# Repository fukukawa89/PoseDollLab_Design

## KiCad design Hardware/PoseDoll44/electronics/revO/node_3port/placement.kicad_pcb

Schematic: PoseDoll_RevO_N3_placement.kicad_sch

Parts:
C1: 10u X5R 25V / CL21A106KAYNNNE; C_0805_2012Metric
C2, C4: 22u X5R 16V / CL21A226MOYNNNE; C_0805_2012Metric
C3, C5, C7, C21, C22, C23: 100n X7R; C_0603_1608Metric
C6: 1u X7R; C_0603_1608Metric
D1: PESD5V0S2BT,215; SOT-23
J1: Fused 5V branch; NOT 12V qualified; JST_PH_B2B-PH-SM4-TB_1x02-1MP_P2.00mm_Vertical
J2: CAN IN / GND-L-H; JST_GH_BM03B-GHS-TBT_1x03-1MP_P1.25mm_Vertical
J3: CAN OUT / GND-L-H; JST_GH_BM03B-GHS-TBT_1x03-1MP_P1.25mm_Vertical
J11: P1 sensor / CS GPIO2; JST_SH_BM06B-SRSS-TB_1x06-1MP_P1.00mm_Vertical
J12: P2 sensor / CS GPIO4; JST_SH_BM06B-SRSS-TB_1x06-1MP_P1.00mm_Vertical
J13: P3 sensor / CS GPIO5; JST_SH_BM06B-SRSS-TB_1x06-1MP_P1.00mm_Vertical
JP1: CAN TERM: close endpoints only; SolderJumper-2_P1.3mm_Open_Pad1.0x1.5mm
L1: LSXND4040TKL2R2MDG / 2.2uH; L_Taiyo-Yuden_NR-40xx
R1, R2, R4, R113, R117, R123, R127, R133, R137: 10k; R_0603_1608Metric
R3, R116, R126, R136: 100k; R_0603_1608Metric
R5: 120R 1% 0.33W / CRCW0603120RFKEAHP; R_0603_1608Metric
R110, R111, R112, R120, R121, R122, R130, R131, R132: 100R; R_0603_1608Metric
R114, R115, R124, R125, R134, R135: 47k; R_0603_1608Metric
TP1: UART_TX; TestPoint_Pad_D1.0mm
TP2: UART_RX; TestPoint_Pad_D1.0mm
TP3: GND; TestPoint_Pad_D1.0mm
TP4: PG; TestPoint_Pad_D1.0mm
TP5: EN; TestPoint_Pad_D1.0mm
TP6: BOOT_N; TestPoint_Pad_D1.0mm
U1: ESP32-S3-WROOM-1-N8; ESP32-S3-WROOM-1
U2: TPS62162DSGR; Texas_DSG0008A_WSON-8-1EP_2x2mm_P0.5mm_EP0.9x1.6mm
U3: TCAN332DR; SOIC-8_3.9x4.9mm_P1.27mm
U11, U12, U13: SN74LVC125APWR; TSSOP-14_4.4x5mm_P0.65mm

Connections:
/+3V3: C2.1, C4.1, C5.1, C7.1, C21.1, C22.1, C23.1, J11.2, J12.2, J13.2, L1.2, R1.1, R2.1, R3.1, R4.1, R113.1, R117.1, R123.1, R127.1, R133.1, R137.1, U1.2 (3V3), U2.6 (VOS), U3.3 (VCC), U11.14 (VCC), U12.14 (VCC), U13.14 (VCC)
/+5V_IN: C1.1, C3.1, J1.1, U2.2 (VIN), U2.3 (EN)
/BOOT_N: R2.2, TP6.1, U1.27 (IO0)
/CAN_H: D1.2 (CAN2), J2.3, J3.3, R5.1, U3.7 (CANH)
/CAN_L: D1.1 (CAN1), J2.2, J3.2, JP1.2 (B), U3.6 (CANL)
/CAN_RX: U1.11 (IO18), U3.4 (RXD)
/CAN_TX: R4.2, U1.10 (IO17), U3.1 (TXD)
/CS1_MCU: R113.2, U1.38 (IO2), U11.1 (1OE_N), U11.4 (2OE_N), U11.10 (3OE_N), U11.12 (4A)
/CS2_MCU: R123.2, U1.4 (IO4), U12.1 (1OE_N), U12.4 (2OE_N), U12.10 (3OE_N), U12.12 (4A)
/CS3_MCU: R133.2, U1.5 (IO5), U13.1 (1OE_N), U13.4 (2OE_N), U13.10 (3OE_N), U13.12 (4A)
/EN: C6.1, R1.2, TP5.1, U1.3 (EN)
/GND: C1.2, C2.2, C3.2, C4.2, C5.2, C6.2, C7.2, C21.2, C22.2, C23.2, D1.3 (GND), J1.2, J2.1, J3.1, J11.1, J12.1, J13.1, R114.2, R115.2, R116.2, R124.2, R125.2, R126.2, R134.2, R135.2, R136.2, TP3.1, U1.1 (GND), U1.40 (GND), U1.41 (GND), U2.1 (PGND), U2.4 (AGND), U2.5 (FB), U2.9 (PAD), U3.2 (GND), U11.7 (GND), U11.13 (4OE_N), U12.7 (GND), U12.13 (4OE_N), U13.7 (GND), U13.13 (4OE_N)
/P1_CS: J11.6, R112.2, R117.2
/P1_CS_DRV: R112.1, U11.11 (4Y)
/P1_MISO: J11.5, R116.1, U11.9 (3A)
/P1_MOSI: J11.4, R111.2, R115.1
/P1_MOSI_DRV: R111.1, U11.6 (2Y)
/P1_SCK: J11.3, R110.2, R114.1
/P1_SCK_DRV: R110.1, U11.3 (1Y)
/P2_CS: J12.6, R122.2, R127.2
/P2_CS_DRV: R122.1, U12.11 (4Y)
/P2_MISO: J12.5, R126.1, U12.9 (3A)
/P2_MOSI: J12.4, R121.2, R125.1
/P2_MOSI_DRV: R121.1, U12.6 (2Y)
/P2_SCK: J12.3, R120.2, R124.1
/P2_SCK_DRV: R120.1, U12.3 (1Y)
/P3_CS: J13.6, R132.2, R137.2
/P3_CS_DRV: R132.1, U13.11 (4Y)
/P3_MISO: J13.5, R136.1, U13.9 (3A)
/P3_MOSI: J13.4, R131.2, R135.1
/P3_MOSI_DRV: R131.1, U13.6 (2Y)
/P3_SCK: J13.3, R130.2, R134.1
/P3_SCK_DRV: R130.1, U13.3 (1Y)
/PG: R3.2, TP4.1, U2.8 (PG)
/SPI_MISO: U1.21 (IO13), U11.8 (3Y), U12.8 (3Y), U13.8 (3Y)
/SPI_MOSI: U1.19 (IO11), U11.5 (2A), U12.5 (2A), U13.5 (2A)
/SPI_SCK: U1.20 (IO12), U11.2 (1A), U12.2 (1A), U13.2 (1A)
/SW_BUCK: L1.1, U2.7 (SW)
/TERM_R: JP1.1 (A), R5.2
/UART_RX: TP2.1, U1.36 (RXD0)
/UART_TX: TP1.1, U1.37 (TXD0)

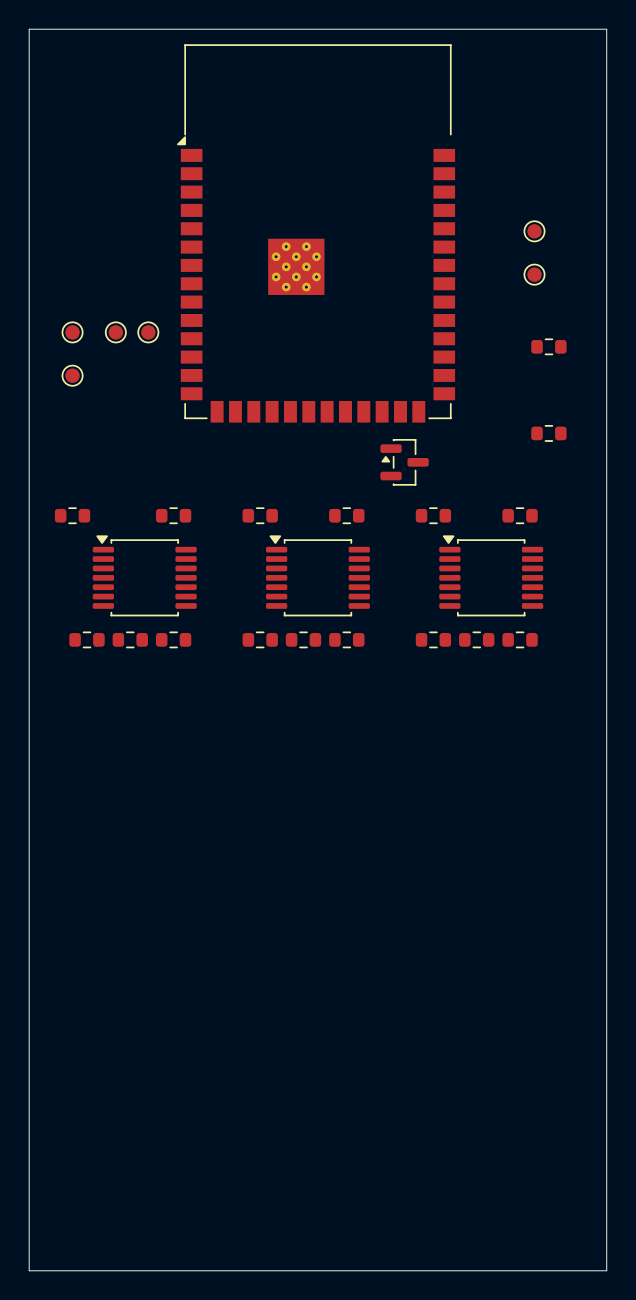
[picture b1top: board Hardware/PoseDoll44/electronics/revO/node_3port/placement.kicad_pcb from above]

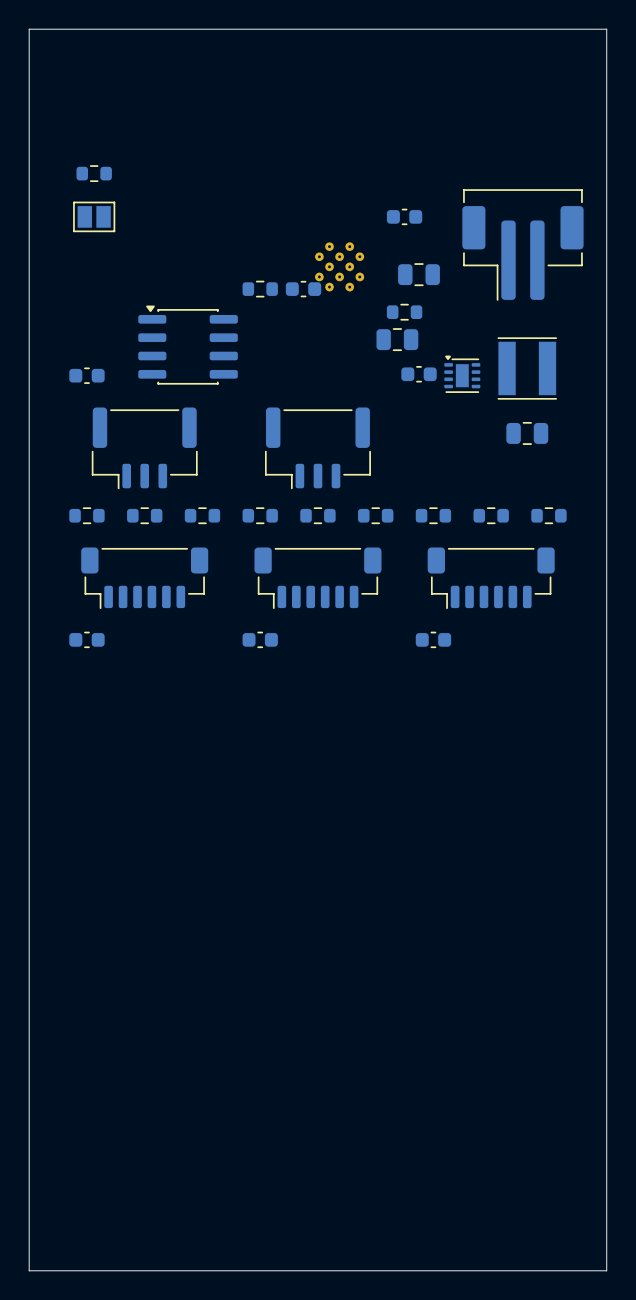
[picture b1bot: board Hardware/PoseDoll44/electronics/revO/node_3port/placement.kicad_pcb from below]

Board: 4 copper layers, 40.0 x 86.0 mm, 60 parts (32 on the bottom side), 41 nets, no tracks yet.

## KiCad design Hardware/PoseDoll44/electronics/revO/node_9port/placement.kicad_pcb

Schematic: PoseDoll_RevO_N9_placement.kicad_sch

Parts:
C1: 10u X5R 25V / CL21A106KAYNNNE; C_0805_2012Metric
C2, C4: 22u X5R 16V / CL21A226MOYNNNE; C_0805_2012Metric
C3, C5, C7, C21, C22, C23, C24, C25, C26, C27, C28, C29: 100n X7R; C_0603_1608Metric
C6: 1u X7R; C_0603_1608Metric
D1: PESD5V0S2BT,215; SOT-23
J1: Fused 5V branch; NOT 12V qualified; JST_PH_B2B-PH-SM4-TB_1x02-1MP_P2.00mm_Vertical
J2: CAN IN / GND-L-H; JST_GH_BM03B-GHS-TBT_1x03-1MP_P1.25mm_Vertical
J3: CAN OUT / GND-L-H; JST_GH_BM03B-GHS-TBT_1x03-1MP_P1.25mm_Vertical
J11: P1 sensor / CS GPIO2; JST_SH_BM06B-SRSS-TB_1x06-1MP_P1.00mm_Vertical
J12: P2 sensor / CS GPIO4; JST_SH_BM06B-SRSS-TB_1x06-1MP_P1.00mm_Vertical
J13: P3 sensor / CS GPIO5; JST_SH_BM06B-SRSS-TB_1x06-1MP_P1.00mm_Vertical
J14: P4 sensor / CS GPIO6; JST_SH_BM06B-SRSS-TB_1x06-1MP_P1.00mm_Vertical
J15: P5 sensor / CS GPIO7; JST_SH_BM06B-SRSS-TB_1x06-1MP_P1.00mm_Vertical
J16: P6 sensor / CS GPIO8; JST_SH_BM06B-SRSS-TB_1x06-1MP_P1.00mm_Vertical
J17: P7 sensor / CS GPIO9; JST_SH_BM06B-SRSS-TB_1x06-1MP_P1.00mm_Vertical
J18: P8 sensor / CS GPIO10; JST_SH_BM06B-SRSS-TB_1x06-1MP_P1.00mm_Vertical
J19: P9 sensor / CS GPIO14; JST_SH_BM06B-SRSS-TB_1x06-1MP_P1.00mm_Vertical
JP1: CAN TERM: close endpoints only; SolderJumper-2_P1.3mm_Open_Pad1.0x1.5mm
L1: LSXND4040TKL2R2MDG / 2.2uH; L_Taiyo-Yuden_NR-40xx
R1, R2, R4, R113, R117, R123, R127, R133, R137, R143, R147, R153, R157, R163, R167, R173, R177, R183, R187, R193, R197: 10k; R_0603_1608Metric
R3, R116, R126, R136, R146, R156, R166, R176, R186, R196: 100k; R_0603_1608Metric
R5: 120R 1% 0.33W / CRCW0603120RFKEAHP; R_0603_1608Metric
R110, R111, R112, R120, R121, R122, R130, R131, R132, R140, R141, R142, R150, R151, R152, R160, R161, R162, R170, R171, R172, R180, R181, R182, R190, R191, R192: 100R; R_0603_1608Metric
R114, R115, R124, R125, R134, R135, R144, R145, R154, R155, R164, R165, R174, R175, R184, R185, R194, R195: 47k; R_0603_1608Metric
TP1: UART_TX; TestPoint_Pad_D1.0mm
TP2: UART_RX; TestPoint_Pad_D1.0mm
TP3: GND; TestPoint_Pad_D1.0mm
TP4: PG; TestPoint_Pad_D1.0mm
TP5: EN; TestPoint_Pad_D1.0mm
TP6: BOOT_N; TestPoint_Pad_D1.0mm
U1: ESP32-S3-WROOM-1-N8; ESP32-S3-WROOM-1
U2: TPS62162DSGR; Texas_DSG0008A_WSON-8-1EP_2x2mm_P0.5mm_EP0.9x1.6mm
U3: TCAN332DR; SOIC-8_3.9x4.9mm_P1.27mm
U11, U12, U13, U14, U15, U16, U17, U18, U19: SN74LVC125APWR; TSSOP-14_4.4x5mm_P0.65mm

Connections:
/+3V3: C2.1, C4.1, C5.1, C7.1, C21.1, C22.1, C23.1, C24.1, C25.1, C26.1, C27.1, C28.1, C29.1, J11.2, J12.2, J13.2, J14.2, J15.2, J16.2, J17.2, J18.2, J19.2, L1.2, R1.1, R2.1, R3.1, R4.1, R113.1, R117.1, R123.1, R127.1, R133.1, R137.1, R143.1, R147.1, R153.1, R157.1, R163.1, R167.1, R173.1, R177.1, R183.1, R187.1, R193.1, R197.1, U1.2 (3V3), U2.6 (VOS), U3.3 (VCC), U11.14 (VCC), U12.14 (VCC), U13.14 (VCC), U14.14 (VCC), U15.14 (VCC), U16.14 (VCC), U17.14 (VCC), U18.14 (VCC), U19.14 (VCC)
/+5V_IN: C1.1, C3.1, J1.1, U2.2 (VIN), U2.3 (EN)
/BOOT_N: R2.2, TP6.1, U1.27 (IO0)
/CAN_H: D1.2 (CAN2), J2.3, J3.3, R5.1, U3.7 (CANH)
/CAN_L: D1.1 (CAN1), J2.2, J3.2, JP1.2 (B), U3.6 (CANL)
/CAN_RX: U1.11 (IO18), U3.4 (RXD)
/CAN_TX: R4.2, U1.10 (IO17), U3.1 (TXD)
/CS1_MCU: R113.2, U1.38 (IO2), U11.1 (1OE_N), U11.4 (2OE_N), U11.10 (3OE_N), U11.12 (4A)
/CS2_MCU: R123.2, U1.4 (IO4), U12.1 (1OE_N), U12.4 (2OE_N), U12.10 (3OE_N), U12.12 (4A)
/CS3_MCU: R133.2, U1.5 (IO5), U13.1 (1OE_N), U13.4 (2OE_N), U13.10 (3OE_N), U13.12 (4A)
/CS4_MCU: R143.2, U1.6 (IO6), U14.1 (1OE_N), U14.4 (2OE_N), U14.10 (3OE_N), U14.12 (4A)
/CS5_MCU: R153.2, U1.7 (IO7), U15.1 (1OE_N), U15.4 (2OE_N), U15.10 (3OE_N), U15.12 (4A)
/CS6_MCU: R163.2, U1.12 (IO8), U16.1 (1OE_N), U16.4 (2OE_N), U16.10 (3OE_N), U16.12 (4A)
/CS7_MCU: R173.2, U1.17 (IO9), U17.1 (1OE_N), U17.4 (2OE_N), U17.10 (3OE_N), U17.12 (4A)
/CS8_MCU: R183.2, U1.18 (IO10), U18.1 (1OE_N), U18.4 (2OE_N), U18.10 (3OE_N), U18.12 (4A)
/CS9_MCU: R193.2, U1.22 (IO14), U19.1 (1OE_N), U19.4 (2OE_N), U19.10 (3OE_N), U19.12 (4A)
/EN: C6.1, R1.2, TP5.1, U1.3 (EN)
/GND: C1.2, C2.2, C3.2, C4.2, C5.2, C6.2, C7.2, C21.2, C22.2, C23.2, C24.2, C25.2, C26.2, C27.2, C28.2, C29.2, D1.3 (GND), J1.2, J2.1, J3.1, J11.1, J12.1, J13.1, J14.1, J15.1, J16.1, J17.1, J18.1, J19.1, R114.2, R115.2, R116.2, R124.2, R125.2, R126.2, R134.2, R135.2, R136.2, R144.2, R145.2, R146.2, R154.2, R155.2, R156.2, R164.2, R165.2, R166.2, R174.2, R175.2, R176.2, R184.2, R185.2, R186.2, R194.2, R195.2, R196.2, TP3.1, U1.1 (GND), U1.40 (GND), U1.41 (GND), U2.1 (PGND), U2.4 (AGND), U2.5 (FB), U2.9 (PAD), U3.2 (GND), U11.7 (GND), U11.13 (4OE_N), U12.7 (GND), U12.13 (4OE_N), U13.7 (GND), U13.13 (4OE_N), U14.7 (GND), U14.13 (4OE_N), U15.7 (GND), U15.13 (4OE_N), U16.7 (GND), U16.13 (4OE_N), U17.7 (GND), U17.13 (4OE_N), U18.7 (GND), U18.13 (4OE_N), U19.7 (GND), U19.13 (4OE_N)
/P1_CS: J11.6, R112.2, R117.2
/P1_CS_DRV: R112.1, U11.11 (4Y)
/P1_MISO: J11.5, R116.1, U11.9 (3A)
/P1_MOSI: J11.4, R111.2, R115.1
/P1_MOSI_DRV: R111.1, U11.6 (2Y)
/P1_SCK: J11.3, R110.2, R114.1
/P1_SCK_DRV: R110.1, U11.3 (1Y)
/P2_CS: J12.6, R122.2, R127.2
/P2_CS_DRV: R122.1, U12.11 (4Y)
/P2_MISO: J12.5, R126.1, U12.9 (3A)
/P2_MOSI: J12.4, R121.2, R125.1
/P2_MOSI_DRV: R121.1, U12.6 (2Y)
/P2_SCK: J12.3, R120.2, R124.1
/P2_SCK_DRV: R120.1, U12.3 (1Y)
/P3_CS: J13.6, R132.2, R137.2
/P3_CS_DRV: R132.1, U13.11 (4Y)
/P3_MISO: J13.5, R136.1, U13.9 (3A)
/P3_MOSI: J13.4, R131.2, R135.1
/P3_MOSI_DRV: R131.1, U13.6 (2Y)
/P3_SCK: J13.3, R130.2, R134.1
/P3_SCK_DRV: R130.1, U13.3 (1Y)
/P4_CS: J14.6, R142.2, R147.2
/P4_CS_DRV: R142.1, U14.11 (4Y)
/P4_MISO: J14.5, R146.1, U14.9 (3A)
/P4_MOSI: J14.4, R141.2, R145.1
/P4_MOSI_DRV: R141.1, U14.6 (2Y)
/P4_SCK: J14.3, R140.2, R144.1
/P4_SCK_DRV: R140.1, U14.3 (1Y)
/P5_CS: J15.6, R152.2, R157.2
/P5_CS_DRV: R152.1, U15.11 (4Y)
/P5_MISO: J15.5, R156.1, U15.9 (3A)
/P5_MOSI: J15.4, R151.2, R155.1
/P5_MOSI_DRV: R151.1, U15.6 (2Y)
/P5_SCK: J15.3, R150.2, R154.1
/P5_SCK_DRV: R150.1, U15.3 (1Y)
/P6_CS: J16.6, R162.2, R167.2
/P6_CS_DRV: R162.1, U16.11 (4Y)
/P6_MISO: J16.5, R166.1, U16.9 (3A)
/P6_MOSI: J16.4, R161.2, R165.1
/P6_MOSI_DRV: R161.1, U16.6 (2Y)
/P6_SCK: J16.3, R160.2, R164.1
/P6_SCK_DRV: R160.1, U16.3 (1Y)
/P7_CS: J17.6, R172.2, R177.2
/P7_CS_DRV: R172.1, U17.11 (4Y)
/P7_MISO: J17.5, R176.1, U17.9 (3A)
/P7_MOSI: J17.4, R171.2, R175.1
/P7_MOSI_DRV: R171.1, U17.6 (2Y)
/P7_SCK: J17.3, R170.2, R174.1
/P7_SCK_DRV: R170.1, U17.3 (1Y)
/P8_CS: J18.6, R182.2, R187.2
/P8_CS_DRV: R182.1, U18.11 (4Y)
/P8_MISO: J18.5, R186.1, U18.9 (3A)
/P8_MOSI: J18.4, R181.2, R185.1
/P8_MOSI_DRV: R181.1, U18.6 (2Y)
/P8_SCK: J18.3, R180.2, R184.1
/P8_SCK_DRV: R180.1, U18.3 (1Y)
/P9_CS: J19.6, R192.2, R197.2
/P9_CS_DRV: R192.1, U19.11 (4Y)
/P9_MISO: J19.5, R196.1, U19.9 (3A)
/P9_MOSI: J19.4, R191.2, R195.1
/P9_MOSI_DRV: R191.1, U19.6 (2Y)
/P9_SCK: J19.3, R190.2, R194.1
/P9_SCK_DRV: R190.1, U19.3 (1Y)
/PG: R3.2, TP4.1, U2.8 (PG)
/SPI_MISO: U1.21 (IO13), U11.8 (3Y), U12.8 (3Y), U13.8 (3Y), U14.8 (3Y), U15.8 (3Y), U16.8 (3Y), U17.8 (3Y), U18.8 (3Y), U19.8 (3Y)
/SPI_MOSI: U1.19 (IO11), U11.5 (2A), U12.5 (2A), U13.5 (2A), U14.5 (2A), U15.5 (2A), U16.5 (2A), U17.5 (2A), U18.5 (2A), U19.5 (2A)
/SPI_SCK: U1.20 (IO12), U11.2 (1A), U12.2 (1A), U13.2 (1A), U14.2 (1A), U15.2 (1A), U16.2 (1A), U17.2 (1A), U18.2 (1A), U19.2 (1A)
/SW_BUCK: L1.1, U2.7 (SW)
/TERM_R: JP1.1 (A), R5.2
/UART_RX: TP2.1, U1.36 (RXD0)
/UART_TX: TP1.1, U1.37 (TXD0)

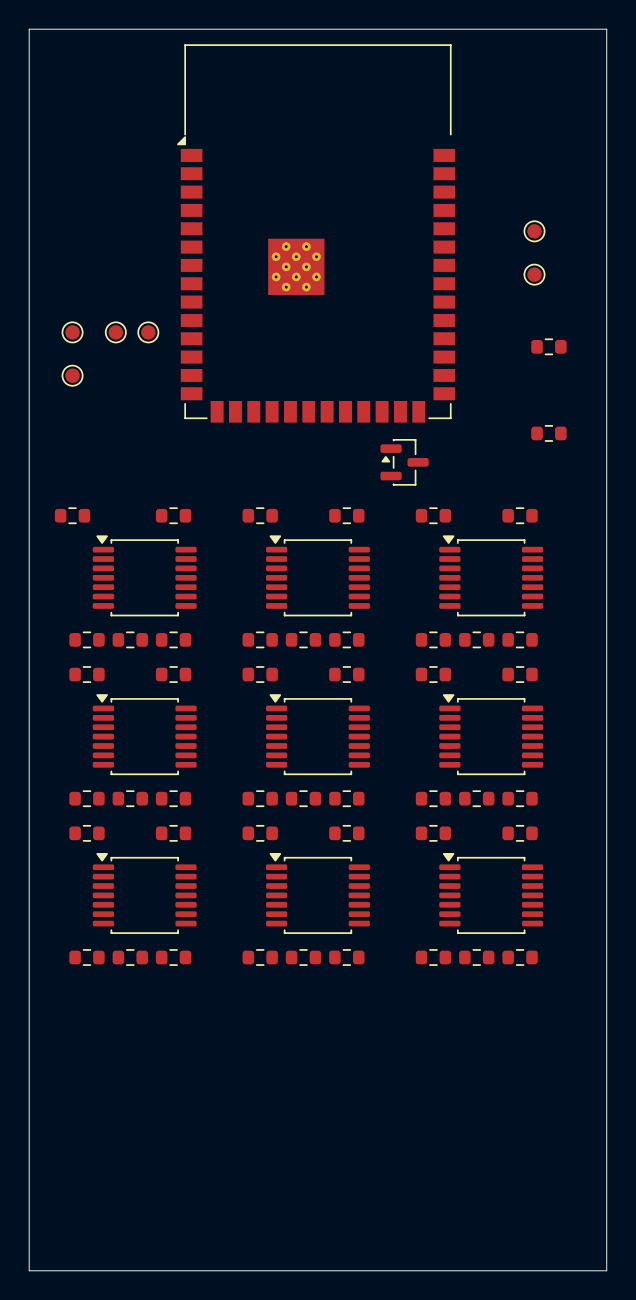
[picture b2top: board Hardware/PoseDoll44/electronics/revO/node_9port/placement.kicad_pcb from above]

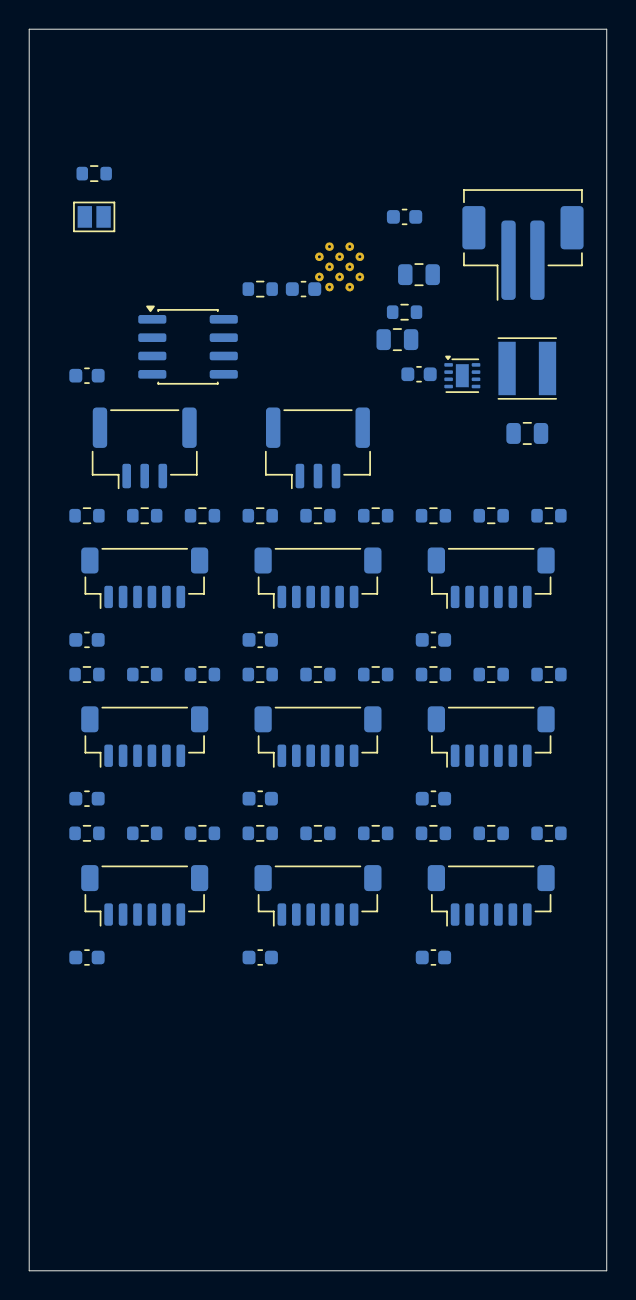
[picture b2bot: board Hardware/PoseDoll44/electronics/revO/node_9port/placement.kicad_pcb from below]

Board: 4 copper layers, 40.0 x 86.0 mm, 126 parts (62 on the bottom side), 89 nets, no tracks yet.

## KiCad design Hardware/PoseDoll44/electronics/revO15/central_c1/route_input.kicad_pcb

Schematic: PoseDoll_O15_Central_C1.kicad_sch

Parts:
C1, C2: 10u X7R 10V; C_0603_1608Metric
C100, C102, C103, C104, C105, C200, C202, C203, C204, C205, C300, C302, C303, C304, C305, C400, C402, C403, C404, C405, C500, C502, C503, C504, C505, C600, C602, C603, C604, C605: 100n X7R 10V; C_0603_1608Metric
C101, C201, C301, C401, C501, C601: 1u X7R 10V; C_0603_1608Metric
D1: SS14 / 1A 40V; D_SMA
J1: CHAIN1 GND,3V3,SCK,MOSI,MISO,CS; JST_GH_SM06B-GHS-TB_1x06-1MP_P1.25mm_Horizontal
J2: CHAIN2 GND,3V3,SCK,MOSI,MISO,CS; JST_GH_SM06B-GHS-TB_1x06-1MP_P1.25mm_Horizontal
J3: CHAIN3 GND,3V3,SCK,MOSI,MISO,CS; JST_GH_SM06B-GHS-TB_1x06-1MP_P1.25mm_Horizontal
J4: CHAIN4 GND,3V3,SCK,MOSI,MISO,CS; JST_GH_SM06B-GHS-TB_1x06-1MP_P1.25mm_Horizontal
J5: CHAIN5 GND,3V3,SCK,MOSI,MISO,CS; JST_GH_SM06B-GHS-TB_1x06-1MP_P1.25mm_Horizontal
J6: CHAIN6 GND,3V3,SCK,MOSI,MISO,CS; JST_GH_SM06B-GHS-TB_1x06-1MP_P1.25mm_Horizontal
J7: 5V INPUT ONLY / JST PH 2; JST_PH_B2B-PH-SM4-TB_1x02-1MP_P2.00mm_Vertical
J8: Pololu D24V22F3 harness: GND, VIN5, VOUT3V3; JST_PH_B3B-PH-SM4-TB_1x03-1MP_P2.00mm_Vertical
Q1, Q2, Q3, Q4, Q5, Q6: 2N7002; SOT-23
R1, R2, R106, R206, R306, R406, R506, R606: 100k; R_0603_1608Metric
R100, R200, R300, R400, R500, R600: 88.7k 1%; R_0603_1608Metric
R101, R108, R109, R110, R201, R208, R209, R210, R301, R308, R309, R310, R401, R408, R409, R410, R501, R508, R509, R510, R601, R608, R609, R610: 47k; R_0603_1608Metric
R102, R107, R202, R207, R302, R307, R402, R407, R502, R507, R602, R607: 10k; R_0603_1608Metric
R103, R104, R105, R203, R204, R205, R303, R304, R305, R403, R404, R405, R503, R504, R505, R603, R604, R605: 100R; R_0603_1608Metric
TP1: P1_FAULT_N; TestPoint_Pad_D1.0mm
TP2: P2_FAULT_N; TestPoint_Pad_D1.0mm
TP3: P3_FAULT_N; TestPoint_Pad_D1.0mm
TP4: P4_FAULT_N; TestPoint_Pad_D1.0mm
TP5: P5_FAULT_N; TestPoint_Pad_D1.0mm
TP6: P6_FAULT_N; TestPoint_Pad_D1.0mm
U1: Seeed XIAO ESP32S3; 2x 1x7 P2.54 male pin strips; XIAO_ESP32S3_2x7_PTH
U100, U200, U300, U400, U500, U600: TPS2553DBVR-1 / latched-off; SOT-23-6
U101, U102, U103, U104, U201, U202, U203, U204, U301, U302, U303, U304, U401, U402, U403, U404, U501, U502, U503, U504, U601, U602, U603, U604: SN74LVC1G125DBVR; SOT-23-5

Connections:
/CS1: R102.2, U1.2 (D1_GPIO2), U103.2 (A), U104.1 (OE_N)
/CS2: R202.2, U1.4 (D3_GPIO4), U203.2 (A), U204.1 (OE_N)
/CS3: R302.2, U1.5 (D4_GPIO5), U303.2 (A), U304.1 (OE_N)
/CS4: R402.2, U1.6 (D5_GPIO6), U403.2 (A), U404.1 (OE_N)
/CS5: R502.2, U1.7 (D6_GPIO43), U503.2 (A), U504.1 (OE_N)
/CS6: R602.2, U1.8 (D7_GPIO44), U603.2 (A), U604.1 (OE_N)
/GND: C1.2, C2.2, C100.2, C101.2, C102.2, C103.2, C104.2, C105.2, C200.2, C201.2, C202.2, C203.2, C204.2, C205.2, C300.2, C301.2, C302.2, C303.2, C304.2, C305.2, C400.2, C401.2, C402.2, C403.2, C404.2, C405.2, C500.2, C501.2, C502.2, C503.2, C504.2, C505.2, C600.2, C601.2, C602.2, C603.2, C604.2, C605.2, J1.1, J2.1, J3.1, J4.1, J5.1, J6.1, J7.2, J8.1, Q1.2 (S), Q2.2 (S), Q3.2 (S), Q4.2 (S), Q5.2 (S), Q6.2 (S), R1.2, R100.2, R106.2, R108.2, R109.2, R200.2, R206.2, R208.2, R209.2, R300.2, R306.2, R308.2, R309.2, R400.2, R406.2, R408.2, R409.2, R500.2, R506.2, R508.2, R509.2, R600.2, R606.2, R608.2, R609.2, U1.13 (GND), U100.2 (GND), U101.3 (GND), U102.3 (GND), U103.3 (GND), U104.3 (GND), U200.2 (GND), U201.3 (GND), U202.3 (GND), U203.3 (GND), U204.3 (GND), U300.2 (GND), U301.3 (GND), U302.3 (GND), U303.3 (GND), U304.3 (GND), U400.2 (GND), U401.3 (GND), U402.3 (GND), U403.3 (GND), U404.3 (GND), U500.2 (GND), U501.3 (GND), U502.3 (GND), U503.3 (GND), U504.3 (GND), U600.2 (GND), U601.3 (GND), U602.3 (GND), U603.3 (GND), U604.3 (GND)
/IO_ENABLE: Q1.1 (G), Q2.1 (G), Q3.1 (G), Q4.1 (G), Q5.1 (G), Q6.1 (G), R1.1, U1.1 (D0_GPIO1)
/MCU_3V3: C103.1, C203.1, C303.1, C403.1, C503.1, C603.1, R2.2, R102.1, R202.1, R302.1, R402.1, R502.1, R602.1, U1.12 (3V3_MCU), U104.5 (VCC), U204.5 (VCC), U304.5 (VCC), U404.5 (VCC), U504.5 (VCC), U604.5 (VCC)
/MCU_5V: D1.1 (K), U1.14 (5V_VBUS)
/MISO: R2.1, U1.10 (D9_GPIO8), U104.4 (Y), U204.4 (Y), U304.4 (Y), U404.4 (Y), U504.4 (Y), U604.4 (Y)
/MOSI: U1.11 (D10_GPIO9), U102.2 (A), U202.2 (A), U302.2 (A), U402.2 (A), U502.2 (A), U602.2 (A)
/P1_3V3: C101.1, C102.1, C104.1, C105.1, J1.2, R101.1, R107.1, U100.6 (OUT), U101.5 (VCC), U102.5 (VCC), U103.5 (VCC)
/P1_CS: J1.6, R105.2, R107.2
/P1_CS_DRV: R105.1, U103.4 (Y)
/P1_FAULT_N: R110.2, TP1.1, U100.4 (FAULT_N)
/P1_ILIM: R100.1, U100.5 (ILIM)
/P1_MISO: J1.5, R106.1, U104.2 (A)
/P1_MOSI: J1.4, R104.2, R109.1
/P1_MOSI_DRV: R104.1, U102.4 (Y)
/P1_OE_N: Q1.3 (D), R101.2, U101.1 (OE_N), U102.1 (OE_N), U103.1 (OE_N)
/P1_SCK: J1.3, R103.2, R108.1
/P1_SCK_DRV: R103.1, U101.4 (Y)
/P2_3V3: C201.1, C202.1, C204.1, C205.1, J2.2, R201.1, R207.1, U200.6 (OUT), U201.5 (VCC), U202.5 (VCC), U203.5 (VCC)
/P2_CS: J2.6, R205.2, R207.2
/P2_CS_DRV: R205.1, U203.4 (Y)
/P2_FAULT_N: R210.2, TP2.1, U200.4 (FAULT_N)
/P2_ILIM: R200.1, U200.5 (ILIM)
/P2_MISO: J2.5, R206.1, U204.2 (A)
/P2_MOSI: J2.4, R204.2, R209.1
/P2_MOSI_DRV: R204.1, U202.4 (Y)
/P2_OE_N: Q2.3 (D), R201.2, U201.1 (OE_N), U202.1 (OE_N), U203.1 (OE_N)
/P2_SCK: J2.3, R203.2, R208.1
/P2_SCK_DRV: R203.1, U201.4 (Y)
/P3_3V3: C301.1, C302.1, C304.1, C305.1, J3.2, R301.1, R307.1, U300.6 (OUT), U301.5 (VCC), U302.5 (VCC), U303.5 (VCC)
/P3_CS: J3.6, R305.2, R307.2
/P3_CS_DRV: R305.1, U303.4 (Y)
/P3_FAULT_N: R310.2, TP3.1, U300.4 (FAULT_N)
/P3_ILIM: R300.1, U300.5 (ILIM)
/P3_MISO: J3.5, R306.1, U304.2 (A)
/P3_MOSI: J3.4, R304.2, R309.1
/P3_MOSI_DRV: R304.1, U302.4 (Y)
/P3_OE_N: Q3.3 (D), R301.2, U301.1 (OE_N), U302.1 (OE_N), U303.1 (OE_N)
/P3_SCK: J3.3, R303.2, R308.1
/P3_SCK_DRV: R303.1, U301.4 (Y)
/P4_3V3: C401.1, C402.1, C404.1, C405.1, J4.2, R401.1, R407.1, U400.6 (OUT), U401.5 (VCC), U402.5 (VCC), U403.5 (VCC)
/P4_CS: J4.6, R405.2, R407.2
/P4_CS_DRV: R405.1, U403.4 (Y)
/P4_FAULT_N: R410.2, TP4.1, U400.4 (FAULT_N)
/P4_ILIM: R400.1, U400.5 (ILIM)
/P4_MISO: J4.5, R406.1, U404.2 (A)
/P4_MOSI: J4.4, R404.2, R409.1
/P4_MOSI_DRV: R404.1, U402.4 (Y)
/P4_OE_N: Q4.3 (D), R401.2, U401.1 (OE_N), U402.1 (OE_N), U403.1 (OE_N)
/P4_SCK: J4.3, R403.2, R408.1
/P4_SCK_DRV: R403.1, U401.4 (Y)
/P5_3V3: C501.1, C502.1, C504.1, C505.1, J5.2, R501.1, R507.1, U500.6 (OUT), U501.5 (VCC), U502.5 (VCC), U503.5 (VCC)
/P5_CS: J5.6, R505.2, R507.2
/P5_CS_DRV: R505.1, U503.4 (Y)
/P5_FAULT_N: R510.2, TP5.1, U500.4 (FAULT_N)
/P5_ILIM: R500.1, U500.5 (ILIM)
/P5_MISO: J5.5, R506.1, U504.2 (A)
/P5_MOSI: J5.4, R504.2, R509.1
/P5_MOSI_DRV: R504.1, U502.4 (Y)
/P5_OE_N: Q5.3 (D), R501.2, U501.1 (OE_N), U502.1 (OE_N), U503.1 (OE_N)
/P5_SCK: J5.3, R503.2, R508.1
/P5_SCK_DRV: R503.1, U501.4 (Y)
/P6_3V3: C601.1, C602.1, C604.1, C605.1, J6.2, R601.1, R607.1, U600.6 (OUT), U601.5 (VCC), U602.5 (VCC), U603.5 (VCC)
/P6_CS: J6.6, R605.2, R607.2
/P6_CS_DRV: R605.1, U603.4 (Y)
/P6_FAULT_N: R610.2, TP6.1, U600.4 (FAULT_N)
/P6_ILIM: R600.1, U600.5 (ILIM)
/P6_MISO: J6.5, R606.1, U604.2 (A)
/P6_MOSI: J6.4, R604.2, R609.1
/P6_MOSI_DRV: R604.1, U602.4 (Y)
/P6_OE_N: Q6.3 (D), R601.2, U601.1 (OE_N), U602.1 (OE_N), U603.1 (OE_N)
/P6_SCK: J6.3, R603.2, R608.1
/P6_SCK_DRV: R603.1, U601.4 (Y)
/SCK: U1.9 (D8_GPIO7), U101.2 (A), U201.2 (A), U301.2 (A), U401.2 (A), U501.2 (A), U601.2 (A)
/SENSOR_3V3: C2.1, C100.1, C200.1, C300.1, C400.1, C500.1, C600.1, J8.3, R110.1, R210.1, R310.1, R410.1, R510.1, R610.1, U100.1 (IN), U100.3 (EN), U200.1 (IN), U200.3 (EN), U300.1 (IN), U300.3 (EN), U400.1 (IN), U400.3 (EN), U500.1 (IN), U500.3 (EN), U600.1 (IN), U600.3 (EN)
/VIN_5V: C1.1, D1.2 (A), J7.1, J8.2

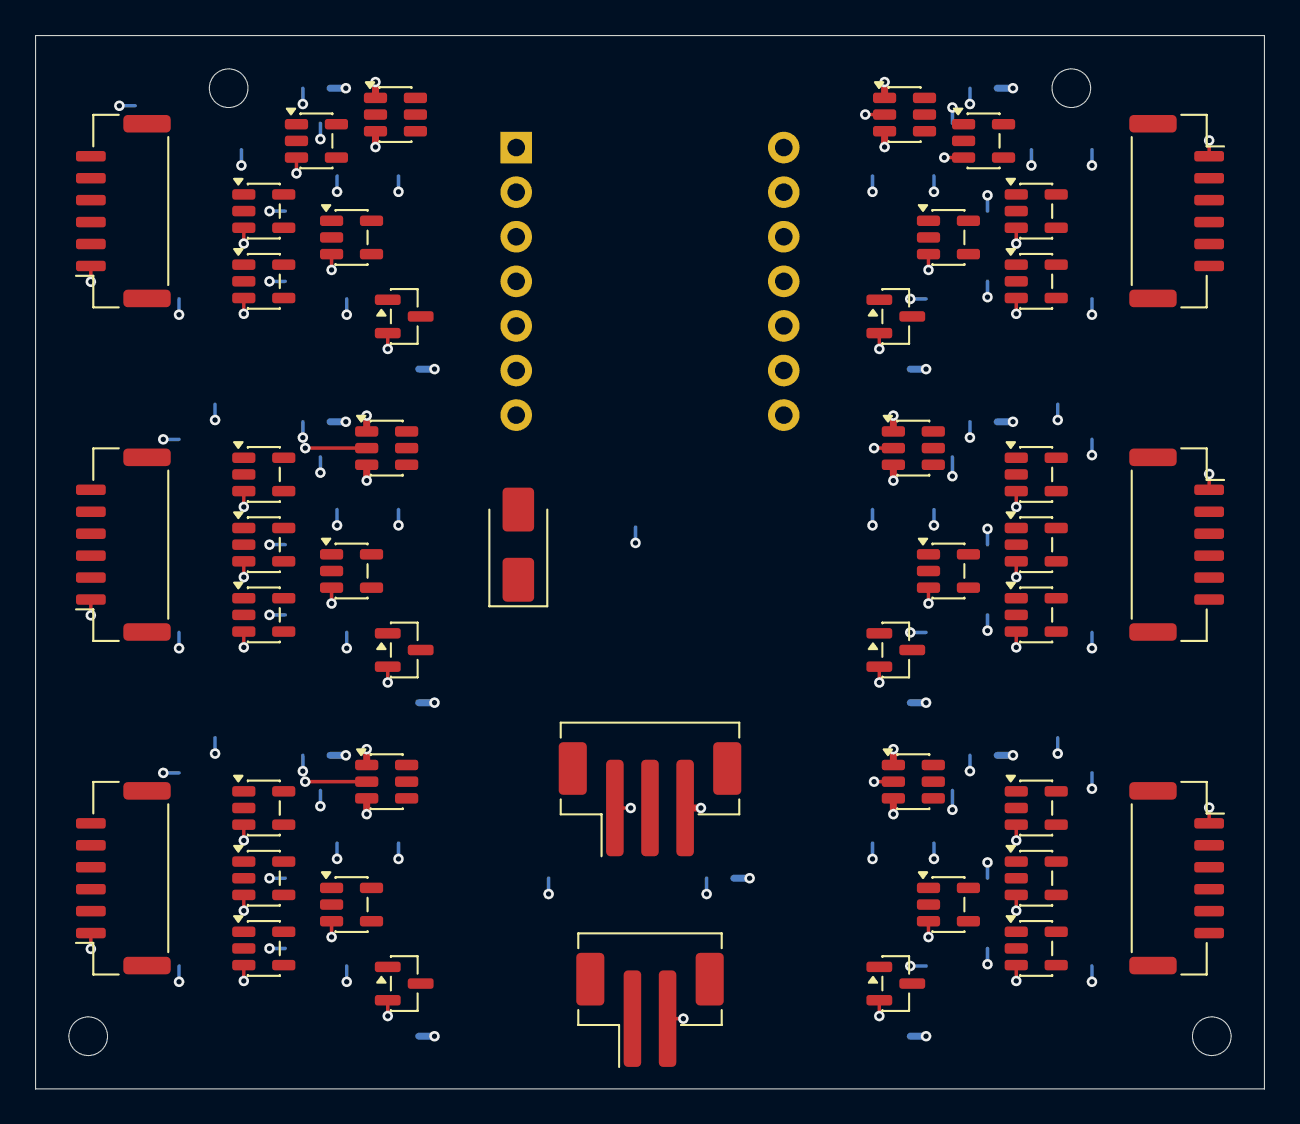
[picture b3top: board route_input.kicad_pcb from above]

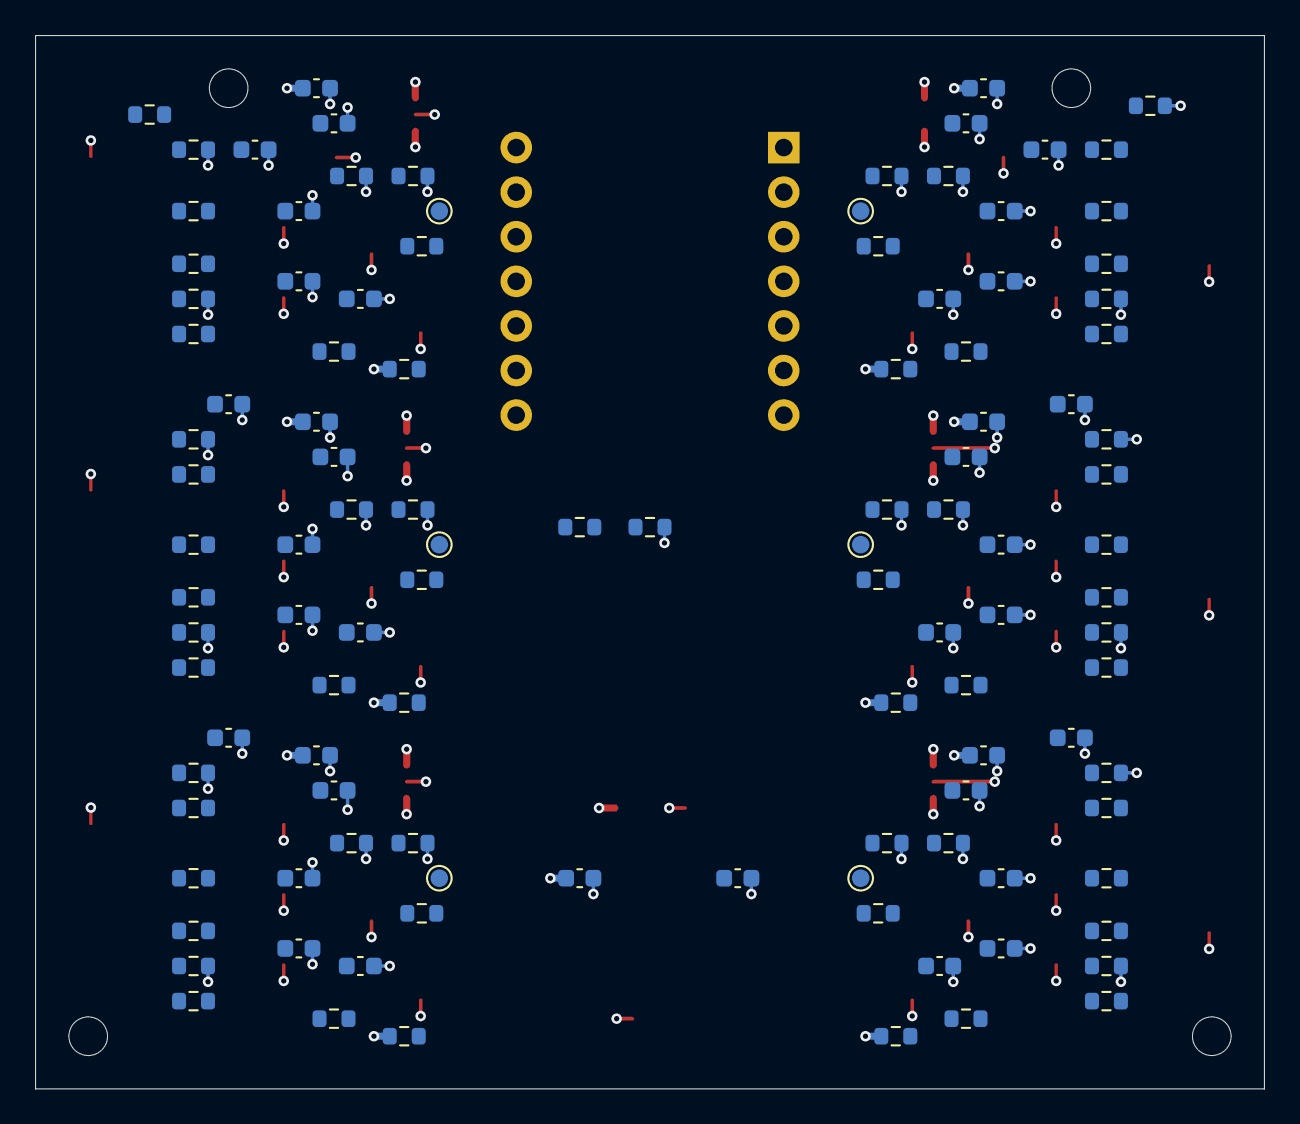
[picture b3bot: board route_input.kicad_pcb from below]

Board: 4 copper layers, 70.0 x 60.0 mm, 162 parts (112 on the bottom side), 81 nets.

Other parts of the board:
H1, H2, H3, H4: MountingHole_2.2mm_M2

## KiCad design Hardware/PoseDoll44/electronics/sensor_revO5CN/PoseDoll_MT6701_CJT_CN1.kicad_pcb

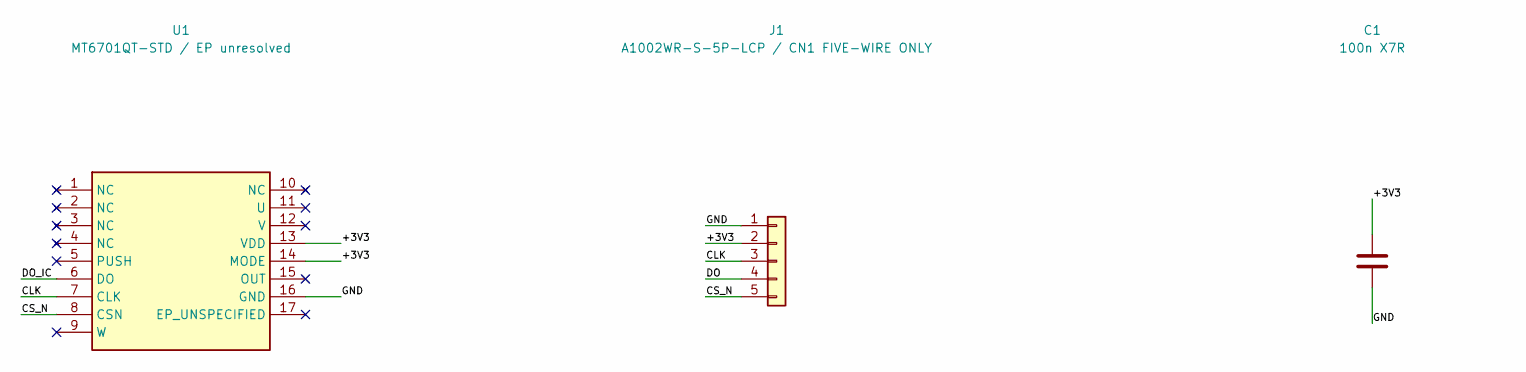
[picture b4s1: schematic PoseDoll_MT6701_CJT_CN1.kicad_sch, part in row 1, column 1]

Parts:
C1: 100n X7R; C_0603_1608Metric
C2: 10u bulk; derating pending; C_0805_2012Metric
J1: A1002WR-S-5P-LCP / CN1 FIVE-WIRE ONLY; CJT_A1002WR_S_5P_LCP
R1: 33R source damping candidate; R_0603_1608Metric
R2: 10k CS safe high; R_0603_1608Metric
U1: MT6701QT-STD / EP unresolved; MT6701QT_QFN16_EP_UNSPECIFIED

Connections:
/+3V3: C1.1, C2.1, J1.2, R2.1, U1.13 (VDD), U1.14 (MODE)
/CLK: J1.3, U1.7 (CLK)
/CS_N: J1.5, R2.2, U1.8 (CSN)
/DO: J1.4, R1.2
/DO_IC: R1.1, U1.6 (DO)
/GND: C1.2, C2.2, J1.1, U1.16 (GND)

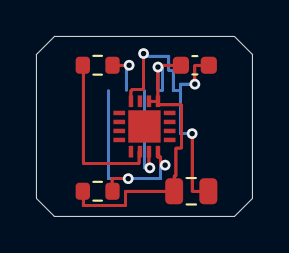
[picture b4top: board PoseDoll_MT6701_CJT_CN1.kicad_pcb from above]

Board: 2 copper layers, 12.0 x 10.0 mm, 6 parts (1 on the bottom side), 6 nets.
